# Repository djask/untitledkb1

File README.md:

# UntitledKb1

 A 5x14 ortholinear board with an STM32 Blackpill. USB port is removed and rotated to face the back, which avoids any issues with trying to fit a usb cable sideways. This board  needs a decent amount of SMD soldering experience for the diodes and USB-C port resistors. 
 
 ## BOM
 - STM32 Blackpill or similar footprint
 - 1x PCB and FR4 plate
 - 40 socket pins and spare through hole wires to socket the STM32
 - 1 Acrylic base cut
 - 2x 5.1k resistors 0402 (can take from stm32 blackpill)
 - 1x 0ohm resistor (optional, just solder copper wire over the pads)
 - 70 Diodes (depends on key count)
 - 70 MX Switches
 - 7mm spacers + some more spacers for the 2nd acrylic panel
 - m2x8 or m2x10 screws x4 (top plate)
 - m2x5 to m2x8 screws x5 (bottom part of plate)
 - Rubber feet (optional)
 - Stabilizers (optional)
 
## Software
See https://github.com/djask/qmk_defs/tree/master/untitledkb1 for a QMK reference config. The board, however, is compatible with any software that supports ARM microcontrollers.

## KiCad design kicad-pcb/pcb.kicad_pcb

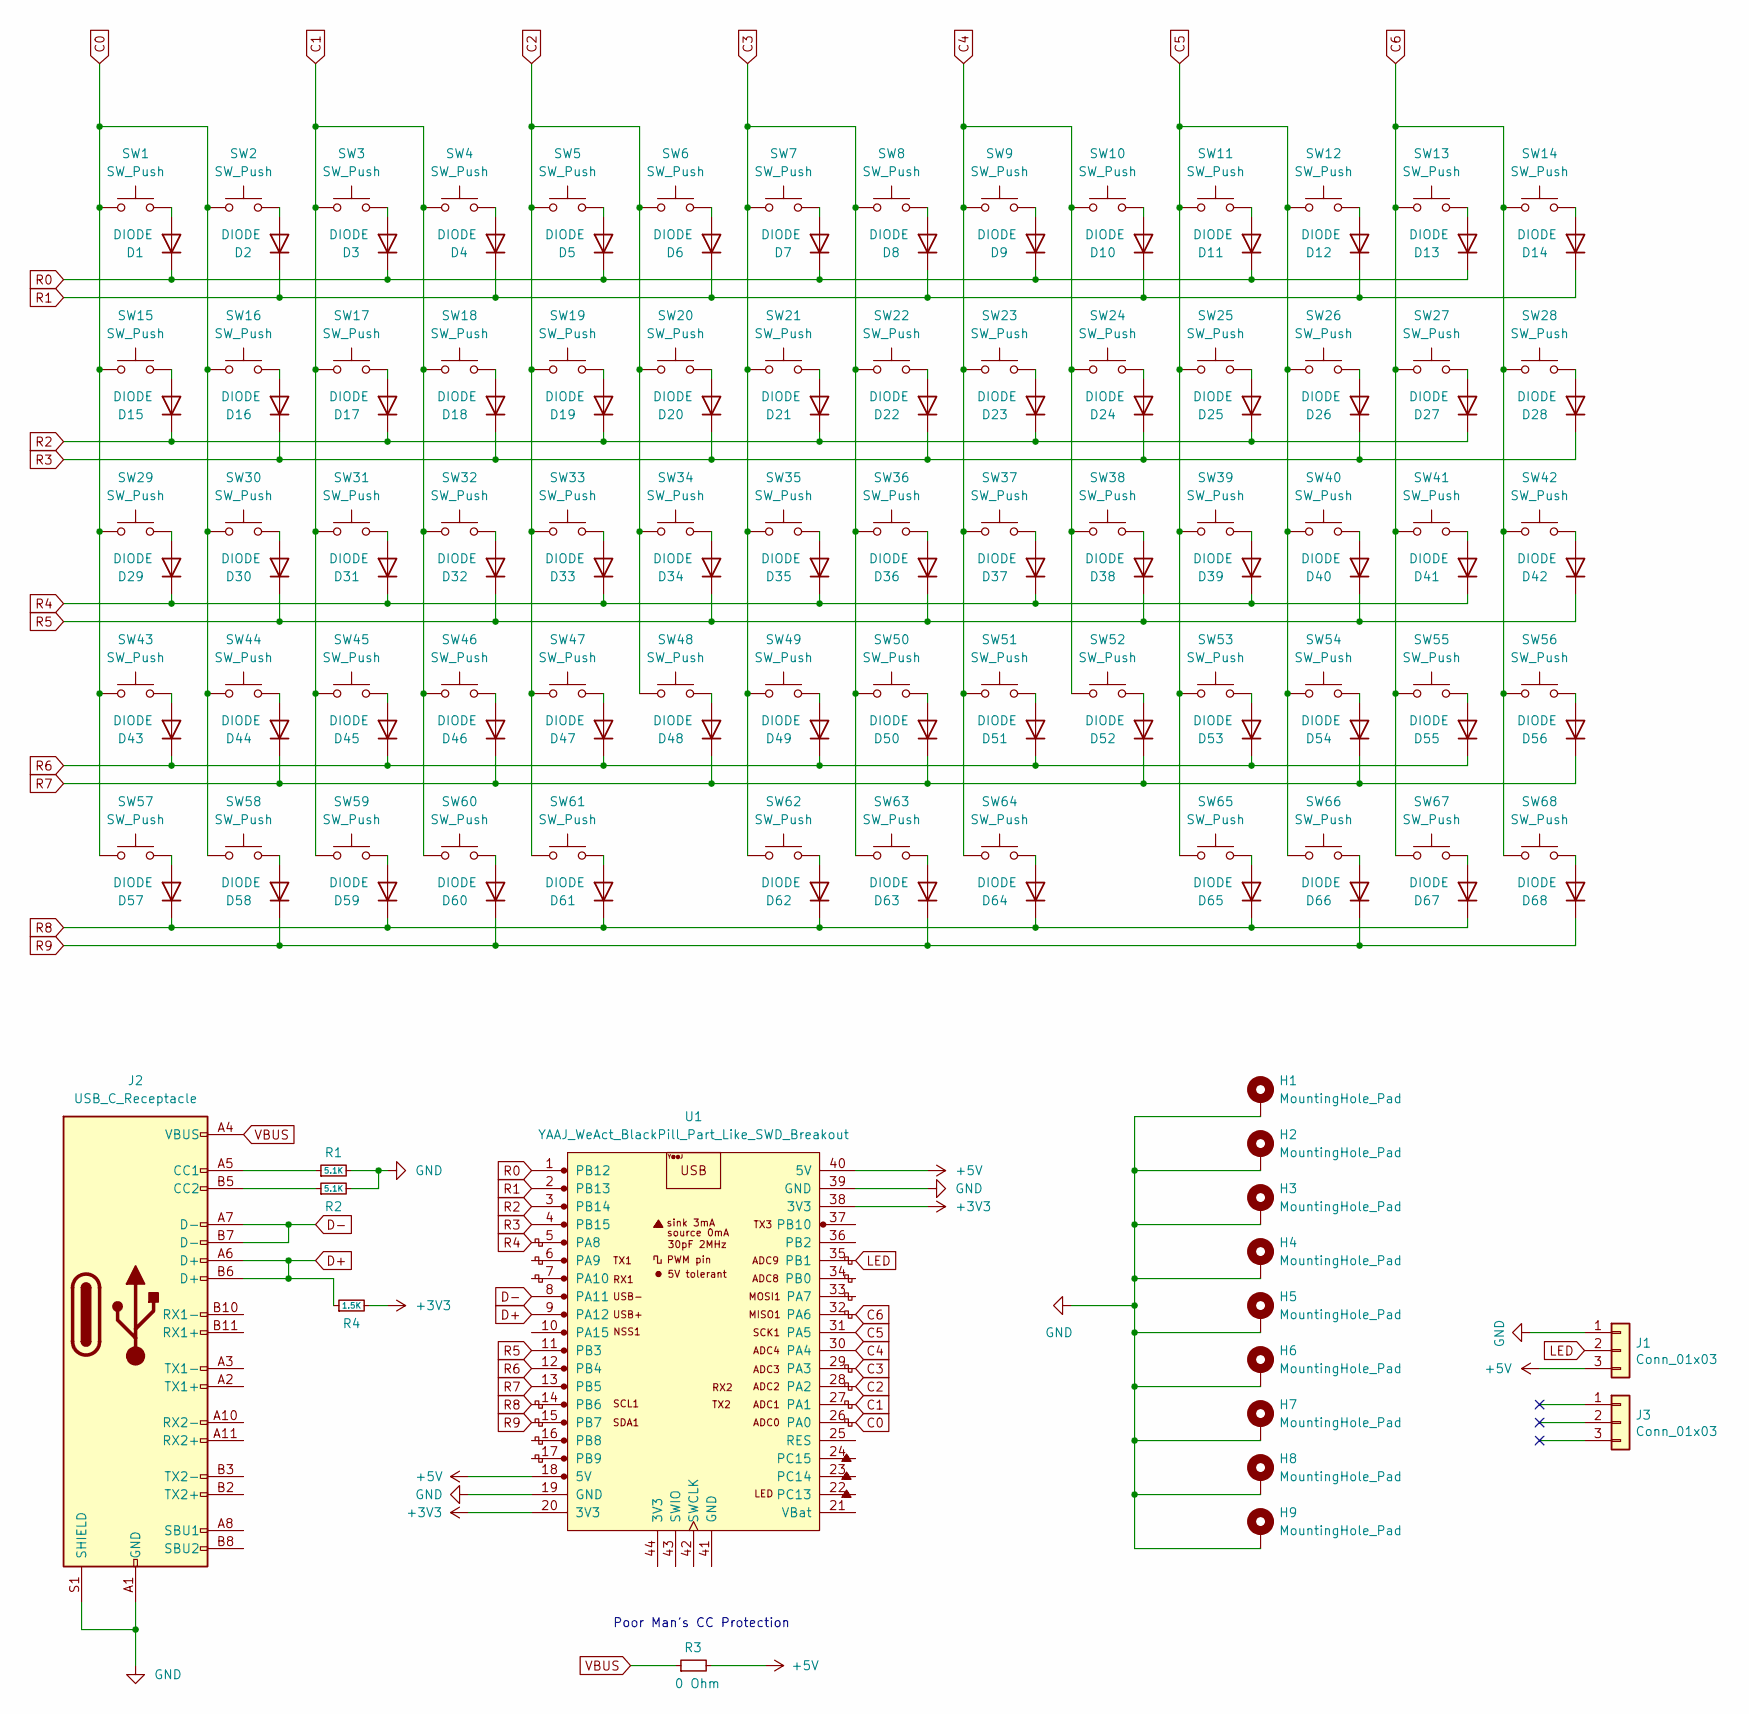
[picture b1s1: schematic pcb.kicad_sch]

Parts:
D1, D2, D3, D4, D5, D6, D7, D8, D9, D10, D11, D12, D13, D14, D15, D16, D17, D18, D19, D20, D21, D22, D23, D24, D25, D26, D27, D28, D29, D30, D31, D32, D33, D34, D35, D36, D37, D38, D39, D40, D41, D42, D43, D44, D45, D46, D47, D48, D49, D50, D51, D52, D53, D54, D55, D56, D57, D58, D59, D60, D61, D62, D63, D64, D65, D66, D67, D68: DIODE; D_SOD123_axial
H1, H2, H3, H4, H5, H6, H7, H8, H9: MountingHole_Pad; Mounting_Hole
J1, J3: Conn_01x03; StripLED_front
J2: USB_C_Receptacle; USB_C_Receptacle_Palconn_UTC16-G
R1, R2: 5.1K; R_0402_1005Metric_Pad0.72x0.64mm_HandSolder
R3: 0 Ohm
R4: 1.5K; R_0402_1005Metric_Pad0.72x0.64mm_HandSolder
SW1, SW2, SW3, SW4, SW5, SW6, SW7, SW8, SW9, SW10, SW11, SW12, SW13, SW14, SW15, SW16, SW17, SW18, SW19, SW20, SW21, SW22, SW23, SW24, SW25, SW26, SW27, SW28, SW29, SW30, SW31, SW32, SW33, SW34, SW35, SW36, SW37, SW38, SW39, SW40, SW41, SW42, SW43, SW44, SW45, SW46, SW47, SW48, SW49, SW50, SW51, SW52, SW53, SW54, SW55, SW56, SW57, SW58, SW59, SW60, SW62, SW63, SW65, SW66, SW67, SW68: SW_Push; MXOnly-1U-NoLED
SW61, SW64: SW_Push; MXOnly-2U-ReversedStabilizers-NoLED
U1: YAAJ_WeAct_BlackPill_Part_Like_SWD_Breakout; YAAJ_WeAct_BlackPill_2

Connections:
+3V3: R4.2, U1.20 (3V3), U1.38 (3V3)
+5V: J1.3, R3.2, U1.18 (5V), U1.40 (5V)
C0: SW1.1, SW2.1, SW15.1, SW16.1, SW29.1, SW30.1, SW43.1, SW44.1, SW57.1, SW58.1, U1.26 (PA0)
C1: SW3.1, SW4.1, SW17.1, SW18.1, SW31.1, SW32.1, SW45.1, SW46.1, SW59.1, SW60.1, U1.27 (PA1)
C2: SW5.1, SW6.1, SW19.1, SW20.1, SW33.1, SW34.1, SW47.1, SW48.1, SW61.1, U1.28 (PA2)
C3: SW7.1, SW8.1, SW21.1, SW22.1, SW35.1, SW36.1, SW49.1, SW50.1, SW62.1, SW63.1, U1.29 (PA3)
C4: SW9.1, SW10.1, SW23.1, SW24.1, SW37.1, SW38.1, SW51.1, SW52.1, SW64.1, U1.30 (PA4)
C5: SW11.1, SW12.1, SW25.1, SW26.1, SW39.1, SW40.1, SW53.1, SW54.1, SW65.1, SW66.1, U1.31 (PA5)
C6: SW13.1, SW14.1, SW27.1, SW28.1, SW41.1, SW42.1, SW55.1, SW56.1, SW67.1, SW68.1, U1.32 (PA6)
D+: J2.A6 (D+), J2.B6 (D+), R4.1, U1.9 (PA12)
D-: J2.A7 (D-), J2.B7 (D-), U1.8 (PA11)
GND: H1.1, H2.1, H3.1, H4.1, H5.1, H6.1, H7.1, H8.1, H9.1, J1.1, J2.A1 (GND), J2.A12 (GND), J2.B1 (GND), J2.B12 (GND), J2.S1 (SHIELD), R1.2, R2.2, U1.19 (GND), U1.39 (GND)
LED: J1.2, U1.35 (PB1)
unnamed: D1.2 (A), SW1.2
unnamed: D2.2 (A), SW2.2
unnamed: D3.2 (A), SW3.2
unnamed: D4.2 (A), SW4.2
unnamed: D5.2 (A), SW5.2
unnamed: D6.2 (A), SW6.2
unnamed: D7.2 (A), SW7.2
unnamed: D8.2 (A), SW8.2
unnamed: D9.2 (A), SW9.2
unnamed: D10.2 (A), SW10.2
unnamed: D11.2 (A), SW11.2
unnamed: D12.2 (A), SW12.2
unnamed: D13.2 (A), SW13.2
unnamed: D14.2 (A), SW14.2
unnamed: D15.2 (A), SW15.2
unnamed: D16.2 (A), SW16.2
unnamed: D17.2 (A), SW17.2
unnamed: D18.2 (A), SW18.2
unnamed: D19.2 (A), SW19.2
unnamed: D20.2 (A), SW20.2
unnamed: D21.2 (A), SW21.2
unnamed: D22.2 (A), SW22.2
unnamed: D23.2 (A), SW23.2
unnamed: D24.2 (A), SW24.2
unnamed: D25.2 (A), SW25.2
unnamed: D26.2 (A), SW26.2
unnamed: D27.2 (A), SW27.2
unnamed: D28.2 (A), SW28.2
unnamed: D29.2 (A), SW29.2
unnamed: D30.2 (A), SW30.2
unnamed: D31.2 (A), SW31.2
unnamed: D32.2 (A), SW32.2
unnamed: D33.2 (A), SW33.2
unnamed: D34.2 (A), SW34.2
unnamed: D35.2 (A), SW35.2
unnamed: D36.2 (A), SW36.2
unnamed: D37.2 (A), SW37.2
unnamed: D38.2 (A), SW38.2
unnamed: D39.2 (A), SW39.2
unnamed: D40.2 (A), SW40.2
unnamed: D41.2 (A), SW41.2
unnamed: D42.2 (A), SW42.2
unnamed: D43.2 (A), SW43.2
unnamed: D44.2 (A), SW44.2
unnamed: D45.2 (A), SW45.2
unnamed: D46.2 (A), SW46.2
unnamed: D47.2 (A), SW47.2
unnamed: D48.2 (A), SW48.2
unnamed: D49.2 (A), SW49.2
unnamed: D50.2 (A), SW50.2
unnamed: D51.2 (A), SW51.2
unnamed: D52.2 (A), SW52.2
unnamed: D53.2 (A), SW53.2
unnamed: D54.2 (A), SW54.2
unnamed: D55.2 (A), SW55.2
unnamed: D56.2 (A), SW56.2
unnamed: D57.2 (A), SW57.2
unnamed: D58.2 (A), SW58.2
unnamed: D59.2 (A), SW59.2
unnamed: D60.2 (A), SW60.2
unnamed: D61.2 (A), SW61.2
unnamed: D62.2 (A), SW62.2
unnamed: D63.2 (A), SW63.2
unnamed: D64.2 (A), SW64.2
unnamed: D65.2 (A), SW65.2
unnamed: D66.2 (A), SW66.2
unnamed: D67.2 (A), SW67.2
unnamed: D68.2 (A), SW68.2
unnamed: J2.A5 (CC1), R1.1
unnamed: J2.B5 (CC2), R2.1
R0: D1.1 (K), D3.1 (K), D5.1 (K), D7.1 (K), D9.1 (K), D11.1 (K), D13.1 (K), U1.1 (PB12)
R1: D2.1 (K), D4.1 (K), D6.1 (K), D8.1 (K), D10.1 (K), D12.1 (K), D14.1 (K), U1.2 (PB13)
R2: D15.1 (K), D17.1 (K), D19.1 (K), D21.1 (K), D23.1 (K), D25.1 (K), D27.1 (K), U1.3 (PB14)
R3: D16.1 (K), D18.1 (K), D20.1 (K), D22.1 (K), D24.1 (K), D26.1 (K), D28.1 (K), U1.4 (PB15)
R4: D29.1 (K), D31.1 (K), D33.1 (K), D35.1 (K), D37.1 (K), D39.1 (K), D41.1 (K), U1.5 (PA8)
R5: D30.1 (K), D32.1 (K), D34.1 (K), D36.1 (K), D38.1 (K), D40.1 (K), D42.1 (K), U1.11 (PB3)
R6: D43.1 (K), D45.1 (K), D47.1 (K), D49.1 (K), D51.1 (K), D53.1 (K), D55.1 (K), U1.12 (PB4)
R7: D44.1 (K), D46.1 (K), D48.1 (K), D50.1 (K), D52.1 (K), D54.1 (K), D56.1 (K), U1.13 (PB5)
R8: D57.1 (K), D59.1 (K), D61.1 (K), D62.1 (K), D64.1 (K), D65.1 (K), D67.1 (K), U1.14 (PB6)
R9: D58.1 (K), D60.1 (K), D63.1 (K), D66.1 (K), D68.1 (K), U1.15 (PB7)
VBUS: J2.A4 (VBUS), J2.A9 (VBUS), J2.B4 (VBUS), J2.B9 (VBUS), R3.1

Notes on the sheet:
Poor Man's CC Protection

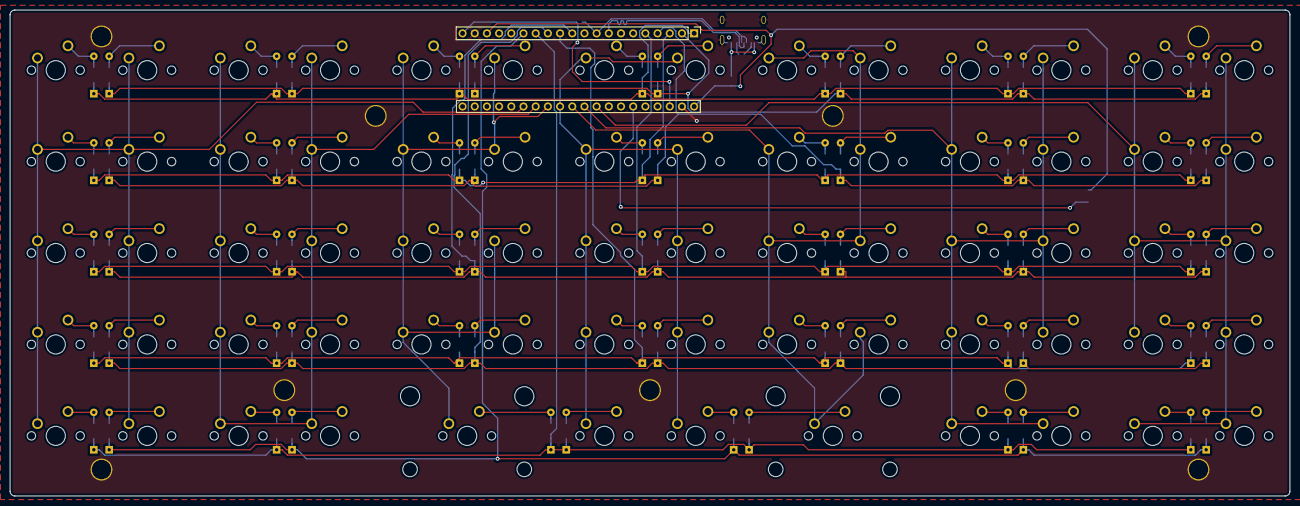
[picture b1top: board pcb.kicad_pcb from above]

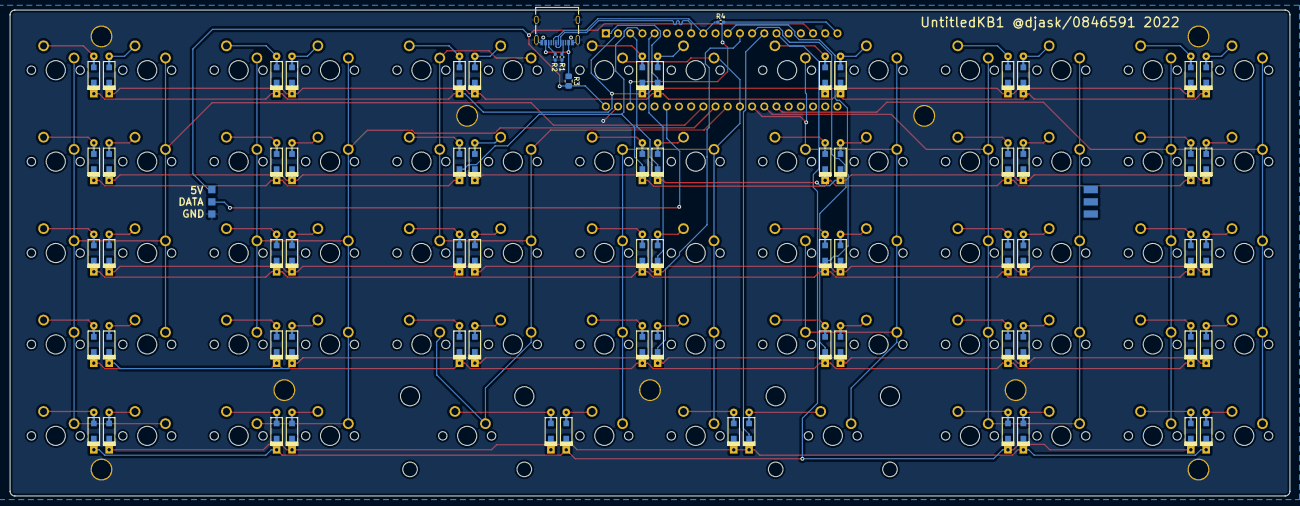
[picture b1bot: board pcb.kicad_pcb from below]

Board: 2 copper layers, 266.7 x 101.2 mm, 153 parts (75 on the bottom side), 94 nets.

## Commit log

2023-01-01 initial upload
2023-01-01 Add backside img
